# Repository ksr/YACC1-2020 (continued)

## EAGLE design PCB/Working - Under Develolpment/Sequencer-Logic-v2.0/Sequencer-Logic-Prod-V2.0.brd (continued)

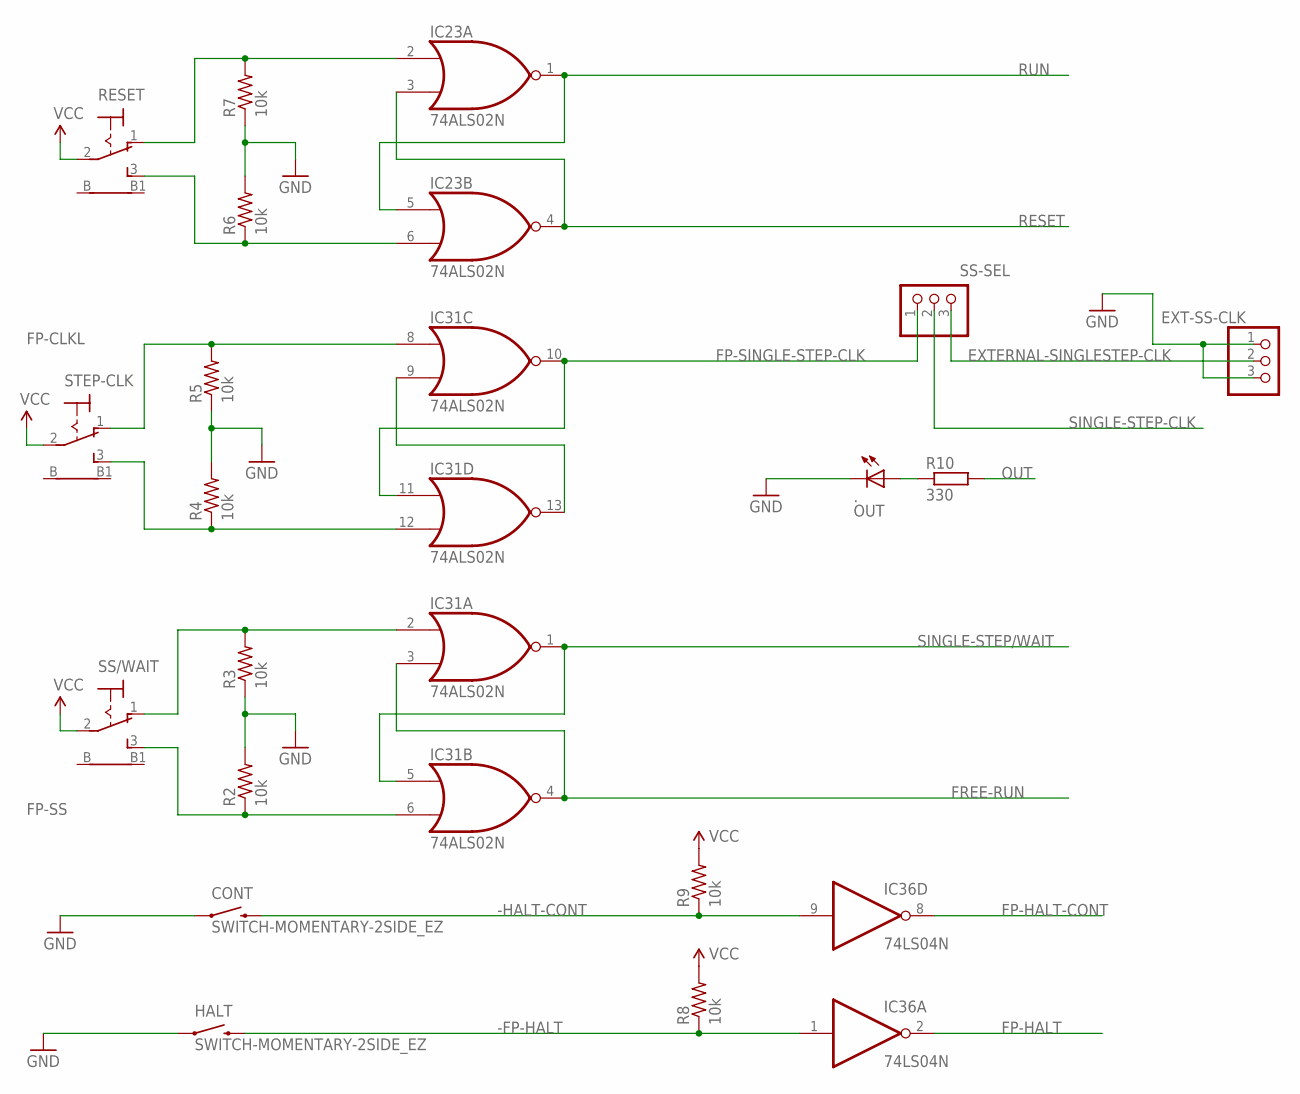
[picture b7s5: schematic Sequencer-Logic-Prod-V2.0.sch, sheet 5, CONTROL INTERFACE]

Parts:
.: OUT; LED5MM
CONT: SWITCH-MOMENTARY-2SIDE_EZ; TACTILE-PTH-SIDEEZ
EXT-SS-CLK: PINHD-1X3; 1X03
HALT: SWITCH-MOMENTARY-2SIDE_EZ; TACTILE-PTH-SIDEEZ
IC23, IC31: 74ALS02N; DIL14
IC36: 74LS04N; DIL14
R2, R3, R4, R5, R6, R7, R8, R9: 10k; 0207/10
R10: 330; 0207/10
RESET: 9070-1W
SS-SEL: PINHD-1X3; 1X03
SS/WAIT: 9070-1W
STEP-CLK: 9070-1W

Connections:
-FP-HALT: HALT.2, IC36.1 (I), R8.1
-HALT-CONT: CONT.2, IC36.9 (I), R9.1
EXTERNAL-SINGLESTEP-CLK: EXT-SS-CLK.2, SS-SEL.3
FP-CLKH: IC31.12 (I1), R4.1, STEP-CLK.3 (S)
FP-CLKL: IC31.8 (I0), R5.2, STEP-CLK.1 (O)
FP-EXECUTE: IC23.6 (I1), R6.1, RESET.3 (S)
FP-FREERUN: IC31.2 (I0), R3.2, SS/WAIT.1 (O)
FP-HALT: IC36.2 (O); also elsewhere on the board
FP-HALT-CONT: IC36.8 (O); also elsewhere on the board
FP-RESET: IC23.2 (I0), R7.2, RESET.1 (O)
FP-SINGLE-STEP-CLK: IC31.10 (O), IC31.11 (I0), SS-SEL.1
FP-SS: IC31.6 (I1), R2.1, SS/WAIT.3 (S)
FREE-RUN: IC31.3 (I1), IC31.4 (O); also elsewhere on the board
GND: ..K (C), CONT.1, EXT-SS-CLK.1, EXT-SS-CLK.3, HALT.1, IC23.7 (GND), IC31.7 (GND), IC36.7 (GND), R2.2, R3.1, R4.2, R5.1, R6.2, R7.1; also elsewhere on the board
HARD-RESET1: IC31.9 (I1), IC31.13 (O)
unnamed: ..A, R10.1
OUT: R10.2; also elsewhere on the board
RESET: IC23.3 (I1), IC23.4 (O); also elsewhere on the board
RUN: IC23.1 (O), IC23.5 (I0); also elsewhere on the board
SINGLE-STEP-CLK: SS-SEL.2; also elsewhere on the board
SINGLE-STEP/WAIT: IC31.1 (O), IC31.5 (I0); also elsewhere on the board
VCC: IC23.14 (VCC), IC31.14 (VCC), IC36.14 (VCC), R8.2, R9.2, RESET.2, SS/WAIT.2, STEP-CLK.2; also elsewhere on the board

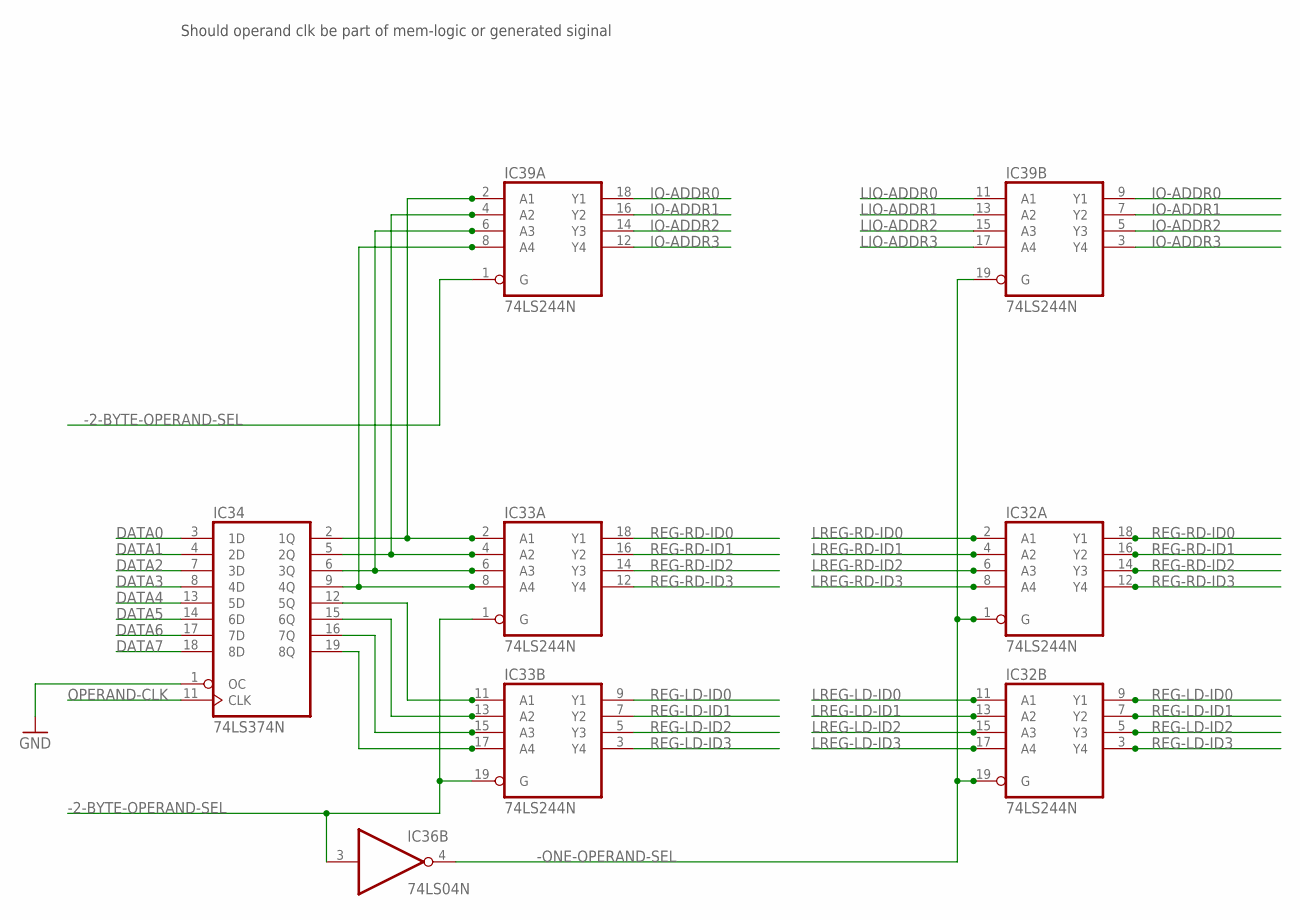
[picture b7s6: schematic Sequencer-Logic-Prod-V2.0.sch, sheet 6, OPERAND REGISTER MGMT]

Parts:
IC32, IC33, IC39: 74LS244N; DIL20
IC34: 74LS374N; DIL20
IC36: 74LS04N; DIL14

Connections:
-2-BYTE-OPERAND-SEL: IC33.1 (G), IC33.19 (G), IC36.3 (I), IC39.1 (G); also elsewhere on the board
-ONE-OPERAND-SEL: IC32.1 (G), IC32.19 (G), IC36.4 (O), IC39.19 (G)
DATA0: IC34.3 (1D); also elsewhere on the board
DATA1: IC34.4 (2D); also elsewhere on the board
DATA2: IC34.7 (3D); also elsewhere on the board
DATA3: IC34.8 (4D); also elsewhere on the board
DATA4: IC34.13 (5D); also elsewhere on the board
DATA5: IC34.14 (6D); also elsewhere on the board
DATA6: IC34.17 (7D); also elsewhere on the board
DATA7: IC34.18 (8D); also elsewhere on the board
GND: IC32.10 (GND), IC33.10 (GND), IC34.1 (OC), IC34.10 (GND), IC36.7 (GND), IC39.10 (GND); also elsewhere on the board
IO-ADDR0: IC39.9 (Y1), IC39.18 (Y1); also elsewhere on the board
IO-ADDR1: IC39.7 (Y2), IC39.16 (Y2); also elsewhere on the board
IO-ADDR2: IC39.5 (Y3), IC39.14 (Y3); also elsewhere on the board
IO-ADDR3: IC39.3 (Y4), IC39.12 (Y4); also elsewhere on the board
LIO-ADDR0: IC39.11 (A1); also elsewhere on the board
LIO-ADDR1: IC39.13 (A2); also elsewhere on the board
LIO-ADDR2: IC39.15 (A3); also elsewhere on the board
LIO-ADDR3: IC39.17 (A4); also elsewhere on the board
LREG-LD-ID0: IC32.11 (A1); also elsewhere on the board
LREG-LD-ID1: IC32.13 (A2); also elsewhere on the board
LREG-LD-ID2: IC32.15 (A3); also elsewhere on the board
LREG-LD-ID3: IC32.17 (A4); also elsewhere on the board
LREG-RD-ID0: IC32.2 (A1); also elsewhere on the board
LREG-RD-ID1: IC32.4 (A2); also elsewhere on the board
LREG-RD-ID2: IC32.6 (A3); also elsewhere on the board
LREG-RD-ID3: IC32.8 (A4); also elsewhere on the board
unnamed: IC33.2 (A1), IC34.2 (1Q), IC39.2 (A1)
unnamed: IC33.4 (A2), IC34.5 (2Q), IC39.4 (A2)
unnamed: IC33.6 (A3), IC34.6 (3Q), IC39.6 (A3)
unnamed: IC33.8 (A4), IC34.9 (4Q), IC39.8 (A4)
unnamed: IC33.11 (A1), IC34.12 (5Q)
unnamed: IC33.13 (A2), IC34.15 (6Q)
unnamed: IC33.15 (A3), IC34.16 (7Q)
unnamed: IC33.17 (A4), IC34.19 (8Q)
OPERAND-CLK: IC34.11 (CLK); also elsewhere on the board
REG-LD-ID0: IC32.9 (Y1), IC33.9 (Y1); also elsewhere on the board
REG-LD-ID1: IC32.7 (Y2), IC33.7 (Y2); also elsewhere on the board
REG-LD-ID2: IC32.5 (Y3), IC33.5 (Y3); also elsewhere on the board
REG-LD-ID3: IC32.3 (Y4), IC33.3 (Y4); also elsewhere on the board
REG-RD-ID0: IC32.18 (Y1), IC33.18 (Y1); also elsewhere on the board
REG-RD-ID1: IC32.16 (Y2), IC33.16 (Y2); also elsewhere on the board
REG-RD-ID2: IC32.14 (Y3), IC33.14 (Y3); also elsewhere on the board
REG-RD-ID3: IC32.12 (Y4), IC33.12 (Y4); also elsewhere on the board
VCC: IC32.20 (VCC), IC33.20 (VCC), IC34.20 (VCC), IC36.14 (VCC), IC39.20 (VCC); also elsewhere on the board

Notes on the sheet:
Should operand clk be part of mem-logic or generated siginal

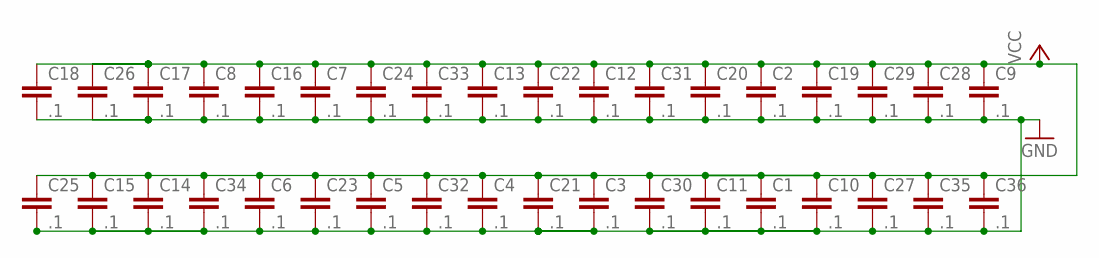
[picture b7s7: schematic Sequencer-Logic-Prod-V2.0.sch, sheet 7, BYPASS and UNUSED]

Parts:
C1, C2, C3, C4, C5, C6, C7, C8, C9, C10, C11, C12, C13, C14, C15, C16, C17, C18, C19, C20, C21, C22, C23, C24, C25, C26, C27, C28, C29, C30, C31, C32, C33, C34, C35, C36: .1; CAP-PTH-SMALLEZ

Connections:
GND: C1.2, C2.2, C3.2, C4.2, C5.2, C6.2, C7.2, C8.2, C9.2, C10.2, C11.2, C12.2, C13.2, C14.2, C15.2, C16.2, C17.2, C18.2, C19.2, C20.2, C21.2, C22.2, C23.2, C24.2, C25.2, C26.2, C27.2, C28.2, C29.2, C30.2, C31.2, C32.2, C33.2, C34.2, C35.2, C36.2; also elsewhere on the board
VCC: C1.1, C2.1, C3.1, C4.1, C5.1, C6.1, C7.1, C8.1, C9.1, C10.1, C11.1, C12.1, C13.1, C14.1, C15.1, C16.1, C17.1, C18.1, C19.1, C20.1, C21.1, C22.1, C23.1, C24.1, C25.1, C26.1, C27.1, C28.1, C29.1, C30.1, C31.1, C32.1, C33.1, C34.1, C35.1, C36.1; also elsewhere on the board

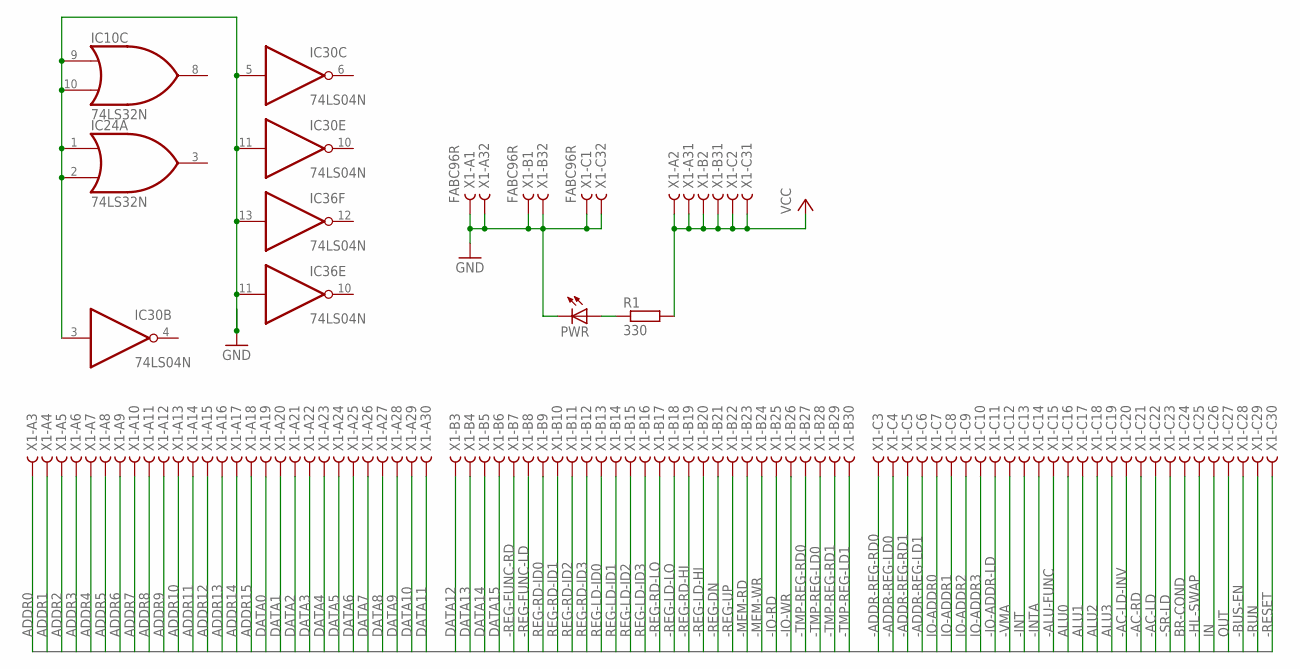
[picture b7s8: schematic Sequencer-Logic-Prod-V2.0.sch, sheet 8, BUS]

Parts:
IC10, IC24: 74LS32N; DIL14
IC30, IC36: 74LS04N; DIL14
PWR: LED5MM
R1: 330; 0207/10
X1: FABC96R

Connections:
-AC-LD: X1.C22; also elsewhere on the board
-AC-LD-INV: X1.C20; also elsewhere on the board
-AC-RD: X1.C21; also elsewhere on the board
-ADDR-REG-LD0: X1.C4; also elsewhere on the board
-ADDR-REG-LD1: X1.C6; also elsewhere on the board
-ADDR-REG-RD0: X1.C3; also elsewhere on the board
-ADDR-REG-RD1: X1.C5; also elsewhere on the board
-ALU-FUNC: X1.C15; also elsewhere on the board
-BUS-EN: X1.C28; also elsewhere on the board
-HL-SWAP: X1.C25; also elsewhere on the board
-INT: X1.C13; also elsewhere on the board
-INTA: X1.C14; also elsewhere on the board
-IO-ADDR-LD: X1.C11; also elsewhere on the board
-IO-RD: X1.B25; also elsewhere on the board
-IO-WR: X1.B26; also elsewhere on the board
-MEM-RD: X1.B23; also elsewhere on the board
-MEM-WR: X1.B24; also elsewhere on the board
-REG-DN: X1.B21; also elsewhere on the board
-REG-FUNC-LD: X1.B8; also elsewhere on the board
-REG-FUNC-RD: X1.B7; also elsewhere on the board
-REG-LD-HI: X1.B20; also elsewhere on the board
-REG-LD-LO: X1.B18; also elsewhere on the board
-REG-RD-HI: X1.B19; also elsewhere on the board
-REG-RD-LO: X1.B17; also elsewhere on the board
-REG-UP: X1.B22; also elsewhere on the board
-RESET: X1.C30; also elsewhere on the board
-RUN: X1.C29
-SR-LD: X1.C23; also elsewhere on the board
-TMP-REG-LD0: X1.B28; also elsewhere on the board
-TMP-REG-LD1: X1.B30; also elsewhere on the board
-TMP-REG-RD0: X1.B27; also elsewhere on the board
-TMP-REG-RD1: X1.B29; also elsewhere on the board
-VMA: X1.C12; also elsewhere on the board
ADDR0: X1.A3
ADDR1: X1.A4
ADDR2: X1.A5
ADDR3: X1.A6
ADDR4: X1.A7
ADDR5: X1.A8
ADDR6: X1.A9
ADDR7: X1.A10
ADDR8: X1.A11
ADDR9: X1.A12
ADDR10: X1.A13
ADDR11: X1.A14
ADDR12: X1.A15
ADDR13: X1.A16
ADDR14: X1.A17
ADDR15: X1.A18
ALU0: X1.C16; also elsewhere on the board
ALU1: X1.C17; also elsewhere on the board
ALU2: X1.C18; also elsewhere on the board
ALU3: X1.C19; also elsewhere on the board
BR-COND: X1.C24; also elsewhere on the board
DATA0: X1.A19; also elsewhere on the board
DATA1: X1.A20; also elsewhere on the board
DATA2: X1.A21; also elsewhere on the board
DATA3: X1.A22; also elsewhere on the board
DATA4: X1.A23; also elsewhere on the board
DATA5: X1.A24; also elsewhere on the board
DATA6: X1.A25; also elsewhere on the board
DATA7: X1.A26; also elsewhere on the board
DATA8: X1.A27; also elsewhere on the board
DATA9: X1.A28; also elsewhere on the board
DATA10: X1.A29; also elsewhere on the board
DATA11: X1.A30; also elsewhere on the board
DATA12: X1.B3; also elsewhere on the board
DATA13: X1.B4; also elsewhere on the board
DATA14: X1.B5; also elsewhere on the board
DATA15: X1.B6; also elsewhere on the board
GND: IC10.7 (GND), IC10.9 (I0), IC10.10 (I1), IC24.1 (I0), IC24.2 (I1), IC24.7 (GND), IC30.3 (I), IC30.5 (I), IC30.7 (GND), IC30.11 (I), IC36.7 (GND), IC36.11 (I), IC36.13 (I), PWR.K (C), X1.A1, X1.A32, X1.B1, X1.B32, X1.C1, X1.C32; also elsewhere on the board
IN: X1.C26
IO-ADDR0: X1.C7; also elsewhere on the board
IO-ADDR1: X1.C8; also elsewhere on the board
IO-ADDR2: X1.C9; also elsewhere on the board
IO-ADDR3: X1.C10; also elsewhere on the board
unnamed: PWR.A, R1.1
OUT: X1.C27; also elsewhere on the board
REG-LD-ID0: X1.B13; also elsewhere on the board
REG-LD-ID1: X1.B14; also elsewhere on the board
REG-LD-ID2: X1.B15; also elsewhere on the board
REG-LD-ID3: X1.B16; also elsewhere on the board
REG-RD-ID0: X1.B9; also elsewhere on the board
REG-RD-ID1: X1.B10; also elsewhere on the board
REG-RD-ID2: X1.B11; also elsewhere on the board
REG-RD-ID3: X1.B12; also elsewhere on the board
VCC: IC10.14 (VCC), IC24.14 (VCC), IC30.14 (VCC), IC36.14 (VCC), R1.2, X1.A2, X1.A31, X1.B2, X1.B31, X1.C2, X1.C31; also elsewhere on the board

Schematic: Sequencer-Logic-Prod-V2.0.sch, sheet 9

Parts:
JP5: PINHD-2X2; 2X02
SV3, SV4: MA20-2

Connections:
-MEM-CPU-RESET: JP5.4
CADDR0: SV4.14; also elsewhere on the board
CADDR1: SV4.16; also elsewhere on the board
CADDR2: SV4.18; also elsewhere on the board
CADDR3: SV4.20; also elsewhere on the board
CADDR4: SV4.22; also elsewhere on the board
CADDR5: SV4.24; also elsewhere on the board
CADDR6: SV4.26; also elsewhere on the board
CADDR7: SV4.28; also elsewhere on the board
CADDR8: SV4.30; also elsewhere on the board
CADDR9: SV4.32; also elsewhere on the board
CADDR10: SV4.34; also elsewhere on the board
CADDR11: SV4.36; also elsewhere on the board
CADDR12: SV4.38; also elsewhere on the board
GND: SV4.39, SV4.40; also elsewhere on the board
READY: SV4.12; also elsewhere on the board
U-2-BYTE-OPERAND-SEL: SV4.10; also elsewhere on the board
U-AC-LD: SV4.7; also elsewhere on the board
U-AC-LD-INV: SV4.3; also elsewhere on the board
U-AC-RD: SV4.5; also elsewhere on the board
U-ADDR-REG-LD0: SV3.16; also elsewhere on the board
U-ADDR-REG-LD1: SV3.20; also elsewhere on the board
U-ADDR-REG-RD0: SV3.14; also elsewhere on the board
U-ADDR-REG-RD1: SV3.18; also elsewhere on the board
U-ALU-FUNC: SV3.34; also elsewhere on the board
U-BRANCH-RD-HI: SV4.2; also elsewhere on the board
U-BRANCH-RD-LO: SV4.35; also elsewhere on the board
U-HL-SWAP: SV4.13; also elsewhere on the board
U-INT-JMP: SV4.6; also elsewhere on the board
U-INTA: SV4.19; also elsewhere on the board
U-IO-ADDR-LD: SV3.30; also elsewhere on the board
U-IO-RD: SV3.39; also elsewhere on the board
U-IO-WR: SV3.4; also elsewhere on the board
U-MEM-RD: SV3.35; also elsewhere on the board
U-MEM-WR: SV3.37; also elsewhere on the board
U-REG-DN: SV3.31; also elsewhere on the board
U-REG-FUNC-LD: SV3.5; also elsewhere on the board
U-REG-FUNC-RD: SV3.3; also elsewhere on the board
U-REG-LD-HI: SV3.29; also elsewhere on the board
U-REG-LD-LO: SV3.25; also elsewhere on the board
U-REG-RD-HI: SV3.27; also elsewhere on the board
U-REG-RD-LO: SV3.23; also elsewhere on the board
U-REG-UP: SV3.33; also elsewhere on the board
U-SOFT-HALT: SV4.8
U-SR-LD: SV4.9; also elsewhere on the board
U-TMP-REG-LD0: SV3.8; also elsewhere on the board
U-TMP-REG-LD1: SV3.12; also elsewhere on the board
U-TMP-REG-RD0: SV3.6; also elsewhere on the board
U-TMP-REG-RD1: SV3.10; also elsewhere on the board
U-VMA: SV3.32; also elsewhere on the board
UALU0: SV3.36; also elsewhere on the board
UALU1: SV3.38; also elsewhere on the board
UALU2: SV3.40; also elsewhere on the board
UALU3: SV4.1; also elsewhere on the board
UBR-TEST: SV4.11; also elsewhere on the board
UBRANCH-LD-HI: SV4.4; also elsewhere on the board
UBRANCH-LD-LO: SV4.37; also elsewhere on the board
UINT-EN: SV4.27; also elsewhere on the board
UINT-LD-HI: SV4.23; also elsewhere on the board
UINT-LD-LO: SV4.21; also elsewhere on the board
UINT-START: SV4.25; also elsewhere on the board
UIO-ADDR0: SV3.22; also elsewhere on the board
UIO-ADDR1: SV3.24; also elsewhere on the board
UIO-ADDR2: SV3.26; also elsewhere on the board
UIO-ADDR3: SV3.28; also elsewhere on the board
ULD-INS-REG: SV4.29; also elsewhere on the board
UOPERAND-CLK: SV4.33; also elsewhere on the board
UOUT-OFF: SV4.15; also elsewhere on the board
UOUT-ON: SV4.17; also elsewhere on the board
UREG-LD-ID0: SV3.15; also elsewhere on the board
UREG-LD-ID1: SV3.17; also elsewhere on the board
UREG-LD-ID2: SV3.19; also elsewhere on the board
UREG-LD-ID3: SV3.21; also elsewhere on the board
UREG-RD-ID0: SV3.7; also elsewhere on the board
UREG-RD-ID1: SV3.9; also elsewhere on the board
UREG-RD-ID2: SV3.11; also elsewhere on the board
UREG-RD-ID3: SV3.13; also elsewhere on the board
USPARE1: JP5.1; also elsewhere on the board
USPARE2: JP5.2; also elsewhere on the board
UUCODE-COUNT-RESET: SV4.31; also elsewhere on the board
VCC: SV3.1, SV3.2; also elsewhere on the board

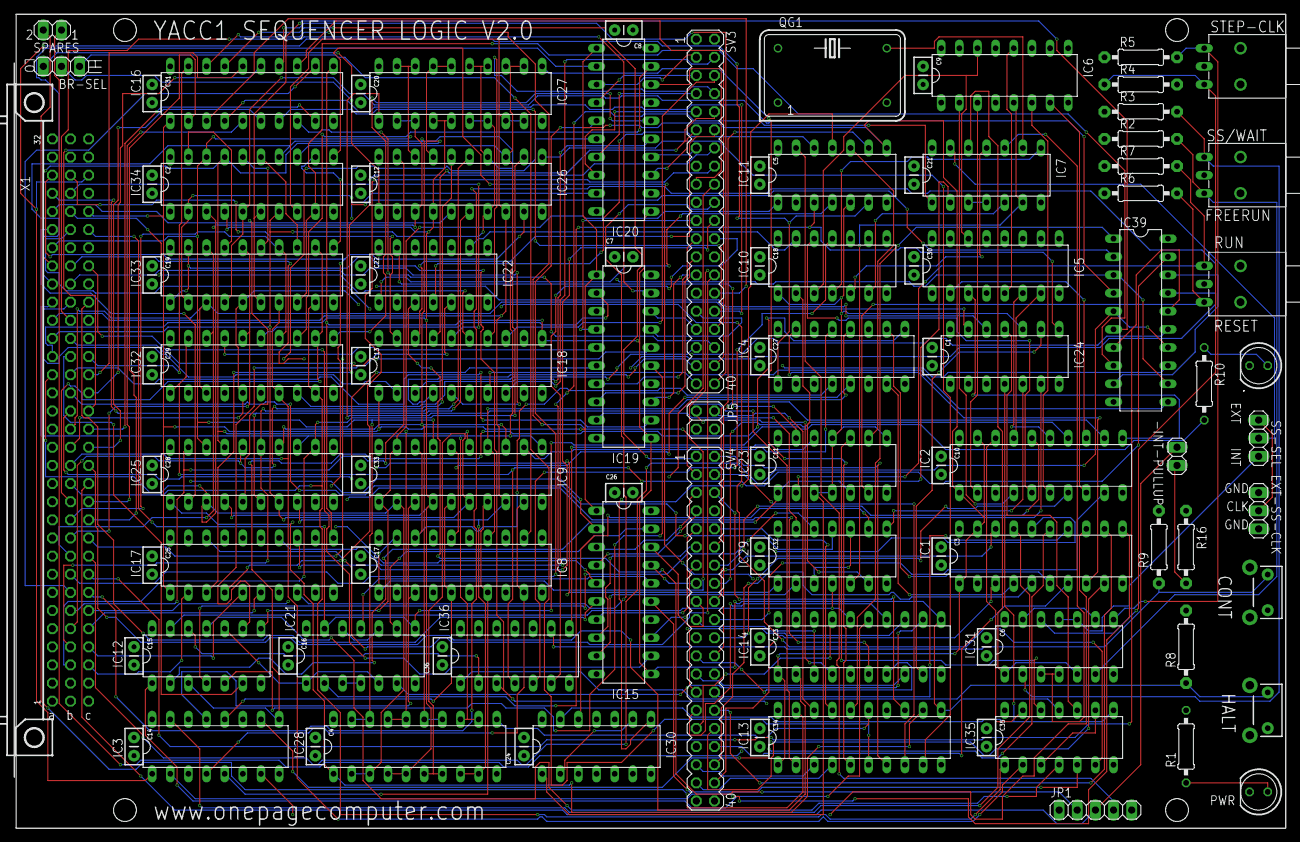
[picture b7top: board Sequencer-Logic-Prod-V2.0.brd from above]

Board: 4 copper layers, 177.8 x 114.0 mm, 102 parts (0 on the bottom side), 274 nets.

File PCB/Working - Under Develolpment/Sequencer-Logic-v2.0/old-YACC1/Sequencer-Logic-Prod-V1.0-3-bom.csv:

"Qty";"Value";"Device";"Package";"Parts";"Description";"MF";"MPN";"OC_FARNELL";"OC_NEWARK";"SPICEMODEL";"SPICEPREFIX";
"3";"";"9070-1W";"9070-1W";"RESET, SS/WAIT, STEP-CLK";"TOGGLE SWITCH";"";"";"";"";"";"";
"2";"";"M10X22X10_LOCK";"2X10_LOCK";"J1, J2";"This was SPECIALLY designed to be used with our Graphic LCD Backpack.  Be sure you want to use this!  It is not only staggered on each line of header holes, but IT IS ALSO offset of the center point of the top and bottom lines by 5 mil.  This causes the headers to lock into place on the "standard" footprint on the LCD screen.  The extra squares on the tdocu layer are there simply to reference other pins (if you were to actually populate a longer header than ten long - this is what we do with the backpacks).";"";"";"";"";"";"";
"2";"";"MA20-2";"MA20-2";"SV1, SV2";"PIN HEADER";"";"";"unknown";"unknown";"";"";
"2";"";"PINHD-1X2";"1X02";"JP2, JP3";"PIN HEADER";"";"";"";"";"";"";
"1";"";"PINHD-1X5";"1X05";"JP1";"PIN HEADER";"";"";"";"";"";"";
"1";"";"XO-14";"DIL14S";"QG1";"CRYSTAL";"";"";"unknown";"unknown";"";"";
"36";".1";"CAPEZ";"CAP-PTH-SMALLEZ";"C1, C2, C3, C4, C5, C6, C7, C8, C9, C10, C11, C12, C13, C14, C15, C16, C17, C18, C19, C20, C21, C22, C23, C24, C25, C26, C27, C28, C29, C30, C31, C32, C33, C34, C35, C36";"Capacitor";"";"";"";"";"";"";
"9";"10k";"R-US_0207/10";"0207/10";"R2, R3, R4, R5, R6, R7, R8, R9, R16";"RESISTOR, American symbol";"";"";"";"";"";"";
"2";"330";"R0207/10";"0207/10";"R1, R10";"RESISTOR, European symbol";"";"";"";"";"NONE";"R";
"3";"74ALS02N";"74ALS02N";"DIL14";"IC21, IC23, IC31";"Quad 2-input NOR gate";"";"";"";"";"";"";
"3";"74LS04N";"74LS04N";"DIL14";"IC11, IC30, IC36";"Hex INVERTER";"";"";"";"";"";"";
"4";"74LS08N";"74LS08N";"DIL14";"IC7, IC12, IC29, IC37";"Quad 2-input AND gate";"";"";"";"";"";"";
"2";"74LS175N";"74LS175N";"DIL16";"IC3, IC4";"Qadruple D type FLIP FLOP, clear";"";"";"";"";"";"";
"2";"74LS192N";"74LS192N";"DIL16";"IC5, IC6";"Synchronous 4-bit UP/DOWN COUNTER";"";"";"";"";"";"";
"6";"74LS244N";"74LS244N";"DIL20";"IC1, IC2, IC8, IC9, IC32, IC33";"Octal BUFFER and LINE DRIVER, 3-state";"";"";"";"";"";"";
"3";"74LS32N";"74LS32N";"DIL14";"IC10, IC24, IC35";"Quad 2-input OR gate";"";"";"";"";"";"";
"13";"74LS374N";"74LS374N";"DIL20";"IC13, IC14, IC15, IC16, IC17, IC18, IC19, IC20, IC25, IC26, IC27, IC28, IC34";"Octal D type transparent LATCH, edge triggered";"";"";"";"";"";"";
"1";"74LS74N";"74LS74N";"DIL14";"IC22";"Dual D type positive edge triggered FLIP FLOP, preset and clear";"";"";"";"";"";"";
"1";"FABC96R";"FABC96R";"FABC96R";"X1";"CONNECTOR female, 96 pins, type R, rows ABC, grid 2.54 mm";"";"";"";"";"";"";
"1";"OUT";"LED5MM";"LED5MM";".";"LED";"";"";"";"";"";"";
"2";"SWITCH-MOMENTARY-2SIDE_EZ";"SWITCH-MOMENTARY-2SIDE_EZ";"TACTILE-PTH-SIDEEZ";"CONT, HALT";"Various NO switches- pushbuttons, reed, etc";"";"";"";"";"";"";
"1";"l1";"LED5MM";"LED5MM";"PWR";"LED";"";"";"";"";"";"";
